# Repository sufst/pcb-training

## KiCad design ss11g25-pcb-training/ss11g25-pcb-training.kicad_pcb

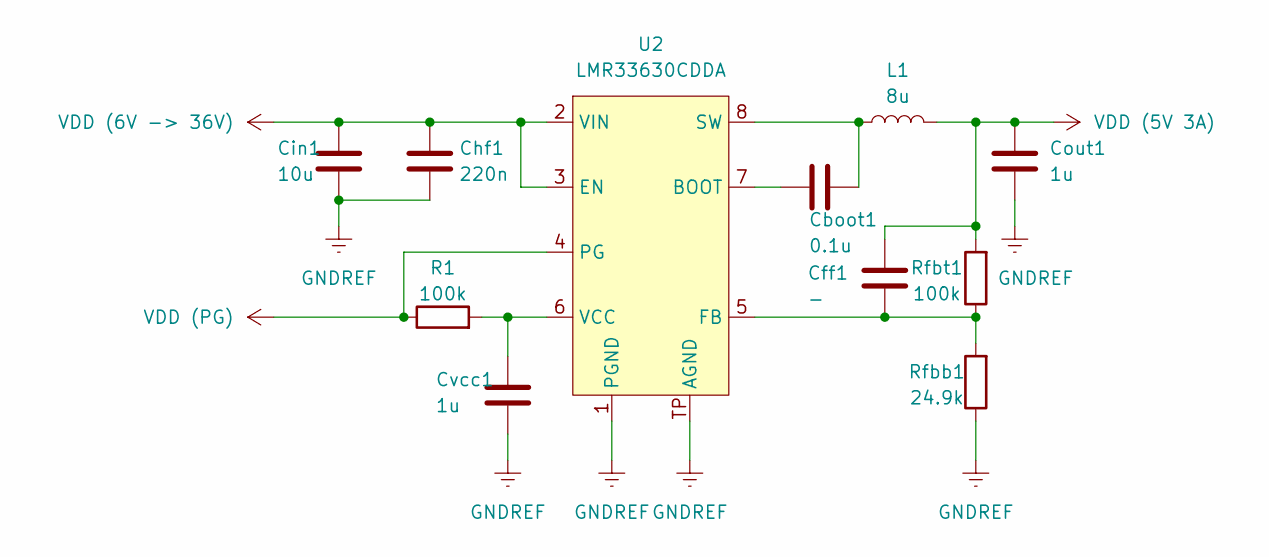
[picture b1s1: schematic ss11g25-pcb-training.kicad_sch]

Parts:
Cboot1: 0.1u; C_0603_1608Metric
Cff1: -; C_0603_1608Metric
Chf1: 220n; C_0603_1608Metric
Cin1: 10u; C_0603_1608Metric
Cout1: 1u; C_0603_1608Metric
Cvcc1: 1u; C_0603_1608Metric
L1: 8u; L_0603_1608Metric
R1: 100k; R_0603_1608Metric
Rfbb1: 24.9k; R_0603_1608Metric
Rfbt1: 100k; R_0603_1608Metric
U2: LMR33630CDDA

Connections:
GNDREF: Chf1.2, Cin1.2, Cout1.2, Cvcc1.2, Rfbb1.1, U2.1 (PGND), U2.TP (AGND)
unnamed: Cboot1.2, U2.7 (BOOT)
unnamed: Cff1.2, Rfbb1.2, Rfbt1.1, U2.5 (FB)
unnamed: Cboot1.1, L1.1, U2.8 (SW)
unnamed: Cvcc1.1, R1.2, U2.6 (VCC)
VDD (5V 3A): Cff1.1, Cout1.1, L1.2, Rfbt1.2
VDD (6V -> 36V): Chf1.1, Cin1.1, U2.2 (VIN), U2.3 (EN)
VDD (PG): R1.1, U2.4 (PG)

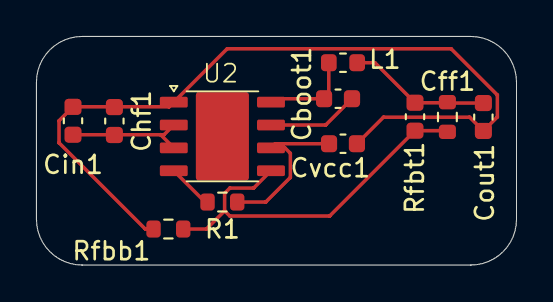
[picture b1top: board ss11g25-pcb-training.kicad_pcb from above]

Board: 2 copper layers, 26.7 x 12.7 mm, 11 parts (0 on the bottom side), 8 nets.

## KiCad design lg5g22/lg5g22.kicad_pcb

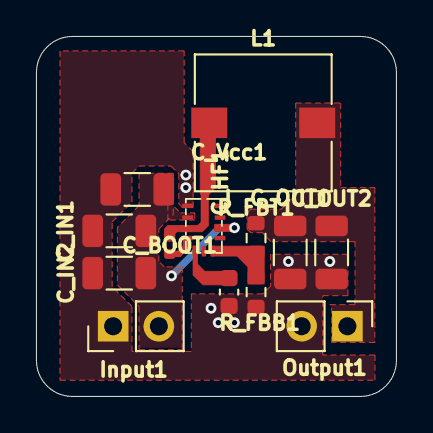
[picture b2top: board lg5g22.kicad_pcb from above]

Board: 2 copper layers, 20.0 x 20.0 mm, 13 parts (0 on the bottom side), 7 nets.

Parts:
C_BOOT1: 0.1uF; C_0402_1005Metric
C_HF1: 220nF; C_1206_3216Metric
C_IN1, C_IN2: 4.7uF; C_1206_3216Metric
C_OUT1, C_OUT2: 22uF; C_1206_3216Metric
C_Vcc1: 1uF; C_0603_1608Metric
Input1: Conn_01x02_Socket; PinHeader_1x02_P2.54mm_Vertical
L1: 10uH; L_Wuerth_WE-PD-Typ-7345
Output1: Conn_01x02_Socket; PinHeader_1x02_P2.54mm_Vertical
R_FBB1: 24.9k; R_0603_1608Metric
R_FBT1: 100k; R_0603_1608Metric
U1: LMR33630CRNX

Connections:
/Vin: C_HF1.1, C_IN1.1, C_IN2.1, Input1.2, U1.2 (VIN), U1.9 (EN)
/Vout: C_OUT1.1, C_OUT2.1, L1.2, Output1.1, R_FBT1.1
GND: C_HF1.2, C_IN1.2, C_IN2.2, C_OUT1.2, C_OUT2.2, C_Vcc1.2, Input1.1, Output1.2, R_FBB1.2, U1.1 (PGND)
unnamed: C_BOOT1.2, U1.4 (BOOT)
unnamed: R_FBB1.1, R_FBT1.2, U1.7 (FB)
unnamed: C_BOOT1.1, L1.1, U1.3 (NC), U1.12 (SW)
unnamed: C_Vcc1.1, U1.5 (VCC)

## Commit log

2025-10-14 KiCAD Tutorial
    hopefully this won't blow anything up
2025-10-14 Tutorial
    Tutorial Session
2025-10-14 testih
2025-10-14 ek2n24
2025-10-14 14October SUFST Meeting
    Initial commit
2025-10-14 created demo
2025-10-14 PCB Training
    Todays work, will add to later, and get the PCB training done!
2025-10-16 Newest updates
2025-10-21 Footpint Fix
    TP Pad fix, so DRC doesn't get mad.
    One error - relating to local save of footprint alter
